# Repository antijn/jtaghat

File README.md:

# jtaghat
Raspberry Pi hat for JTAG debug

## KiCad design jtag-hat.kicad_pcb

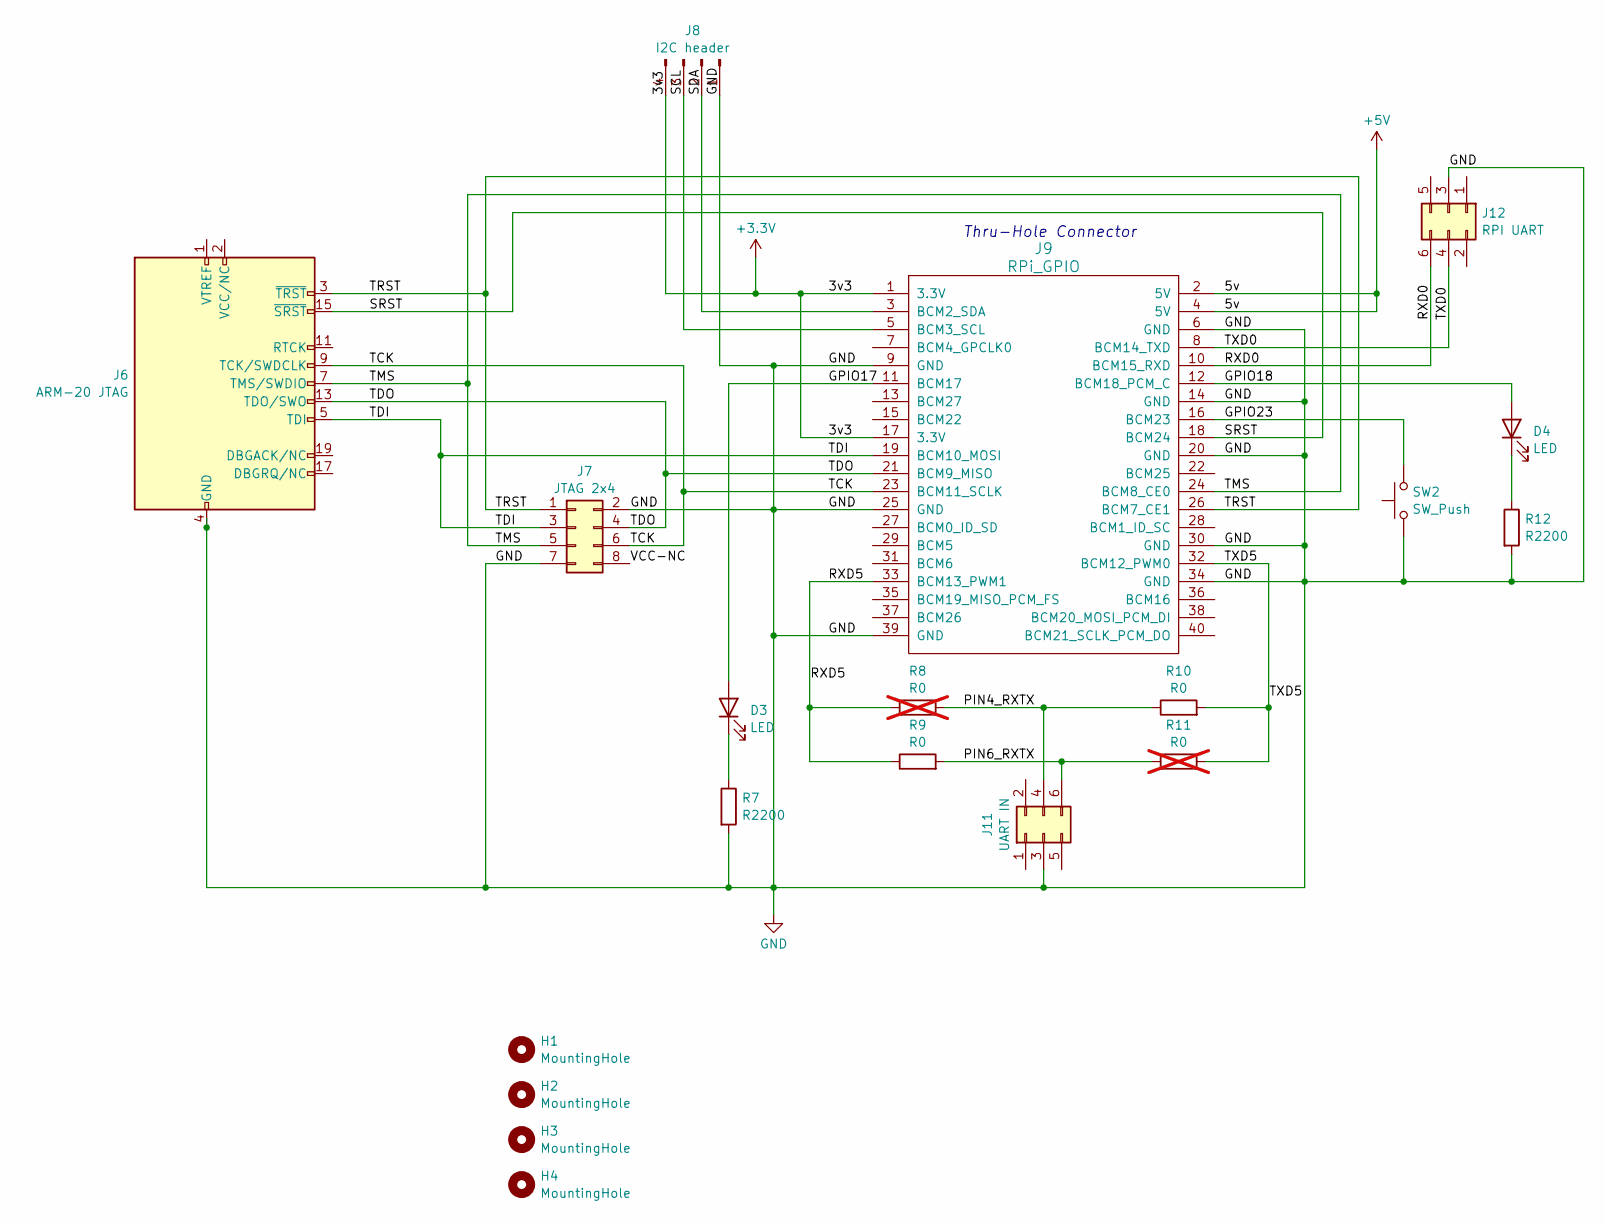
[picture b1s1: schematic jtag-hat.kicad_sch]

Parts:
D3, D4: LED; LED_0805_2012Metric_Pad1.15x1.40mm_HandSolder
H1, H2, H3, H4: MountingHole; MountingHole_3.2mm_M3
J6: ARM-20 JTAG; PinHeader_2x10_P2.54mm_Vertical
J7: JTAG 2x4; PinHeader_2x04_P2.00mm_Vertical_SMD
J8: I2C header; PinHeader_1x04_P2.54mm_Vertical
J9: RPi_GPIO; PinHeader_2x20_P2.54mm_Vertical
J11: UART IN; PinHeader_2x03_P2.00mm_Vertical_SMD
J12: RPI UART; PinHeader_2x03_P2.00mm_Vertical_SMD
R7, R12: R2200; R_0402_1005Metric_Pad0.72x0.64mm_HandSolder
R8, R11: R0; R_0402_1005Metric_Pad0.72x0.64mm_HandSolder; not fitted
R9, R10: R0; R_0402_1005Metric_Pad0.72x0.64mm_HandSolder
SW2: SW_Push; SW_PUSH_6mm

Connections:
+3.3V: J8.4, J9.1 (3.3V), J9.17 (3.3V)
+5V: J9.2 (5V), J9.4 (5V)
/GPIO17: D3.2 (A), J9.11 (BCM17)
/GPIO18: D4.2 (A), J9.12 (BCM18_PCM_C)
/GPIO23: J9.16 (BCM23), SW2.2
/PIN4_RXTX: J11.4, R8.2, R10.1
/PIN6_RXTX: J11.6, R9.2, R11.1
/RXD0: J9.10 (BCM15_RXD), J12.6
/RXD5: J9.33 (BCM13_PWM1), R8.1, R9.1
/SCL: J8.3, J9.5 (BCM3_SCL)
/SDA: J8.2, J9.3 (BCM2_SDA)
/SRST: J6.15 (~SRST), J9.18 (BCM24)
/TCK: J6.9 (TCK/SWDCLK), J7.6, J9.23 (BCM11_SCLK)
/TDI: J6.5 (TDI), J7.3, J9.19 (BCM10_MOSI)
/TDO: J6.13 (TDO/SWO), J7.4, J9.21 (BCM9_MISO)
/TMS: J6.7 (TMS/SWDIO), J7.5, J9.24 (BCM8_CE0)
/TRST: J6.3 (~TRST), J7.1, J9.26 (BCM7_CE1)
/TXD0: J9.8 (BCM14_TXD), J12.4
/TXD5: J9.32 (BCM12_PWM0), R10.2, R11.2
/VCC-NC: J7.8
GND: J6.4 (GND), J6.6 (GND), J6.8 (GND), J6.10 (GND), J6.12 (GND), J6.14 (GND), J6.16 (GND), J6.18 (GND), J6.20 (GND), J7.2, J7.7, J8.1, J9.6 (GND), J9.9 (GND), J9.14 (GND), J9.20 (GND), J9.25 (GND), J9.30 (GND), J9.34 (GND), J9.39 (GND), J11.3, J12.3, R7.2, R12.2, SW2.1
unnamed: D3.1 (K), R7.1
unnamed: D4.1 (K), R12.1

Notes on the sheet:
Thru-Hole Connector

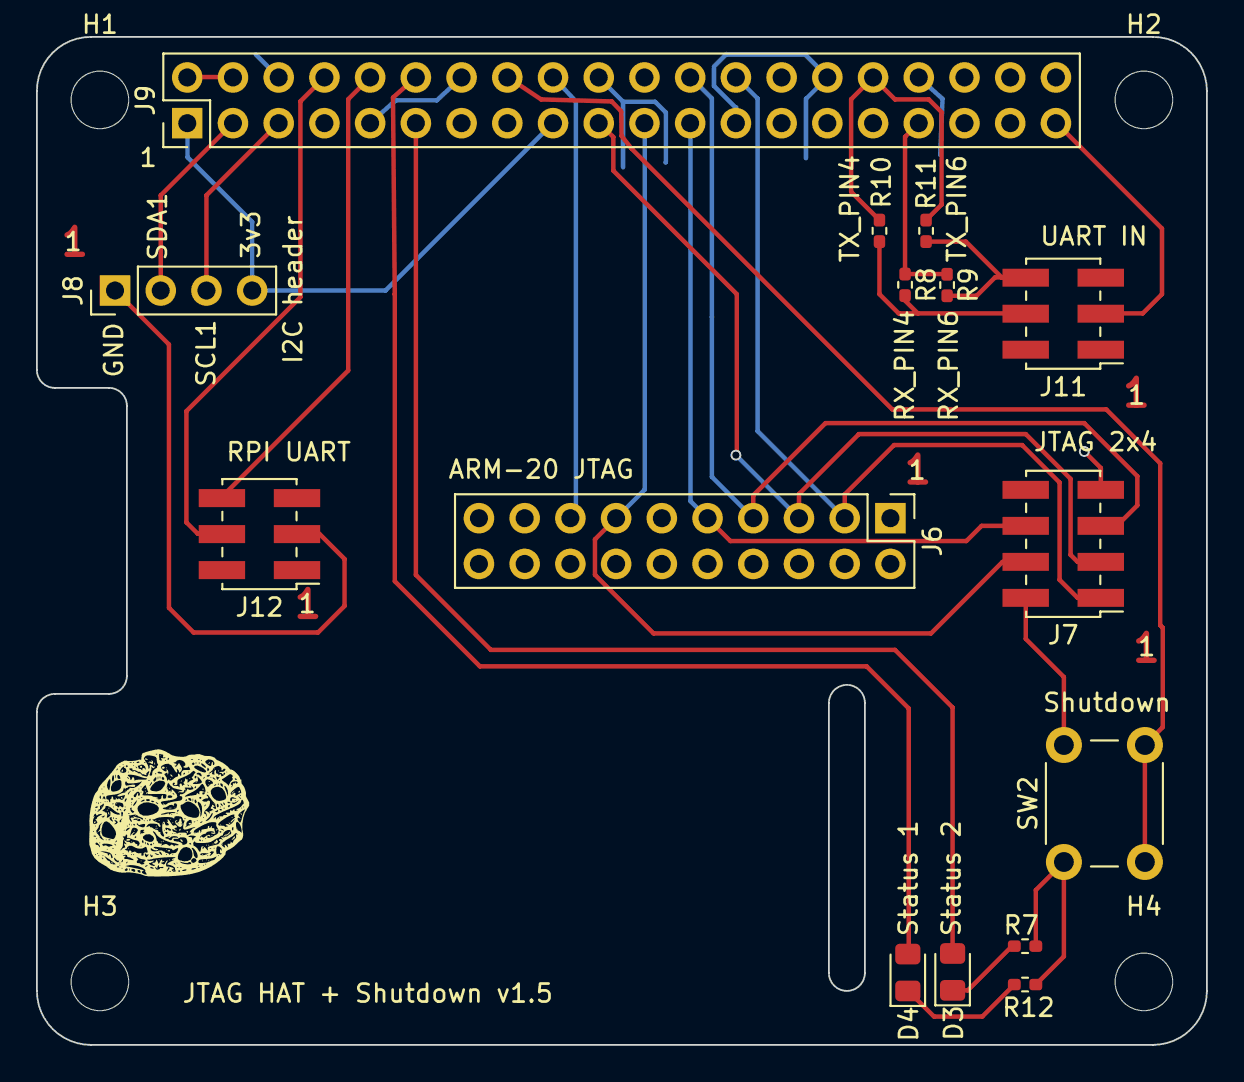
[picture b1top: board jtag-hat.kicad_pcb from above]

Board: 2 copper layers, 65.0 x 56.0 mm, 19 parts (0 on the bottom side), 22 nets.

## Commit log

2023-11-13 v1.2
2023-11-24 v1.3
    - Swapped the JTAG connector placements for connecting convenience
    - Changed resistors to 0402
    - Removed silkscreen around unused PI-header holes
2024-01-04 v1.4
    - Rotate rpi uart header
    - Add second status led
    - Minor cleanup
2024-01-04 v1.5
    - Changed mounting holes to 3.2mm (for M3)
    - Swapped Pi-header for a straight pin-header
    - Converted schematic from sub-schematic
